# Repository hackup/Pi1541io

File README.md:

# PI1541 IO Adapter

This is an IO adapter board for the Raspberry Pi 3, based on the awesome [Pi1541
project](https://cbm-pi1541.firebaseapp.com/) by Steve White. It is currently
very much work in progress. **USE AT YOUR OWN RISK!**

Details of the adapter board development are [documented on hackup.net](https://www.hackup.net/tag/pi1541/). The [Gerber files](gerber/Pi1541io-rev4.zip) for the latest stable revision are included in the repository. Also, the boards are ready to be ordered directly from [PCBWay](https://www.pcbway.com/project/shareproject/Pi1541_IO_Adapter__Rev_4.html?inviteid=78096) or [DirtyPCBs](https://dirtypcbs.com/store/designer/details/hackup/6112/pi1541-io-adapter-rev-4).

## Revisions

### Revision 4
This revision of the board resolves the I2C power supply issues of the previous version. All relevant aspects of the I2C header must now be configured using solder bridges on the bottom side of the PCB.

* Select either 3.3V or 5V power supply. (If in doubt, use 3.3V!)
* Pin order: Vin-GND-SCL-SDA or GND-Vin-SCL-SDA
* Chose either I2C bus 0 or 1

See [here](https://www.hackup.net/2018/07/pi1541io-revision-4/) for more details.

### Revision 3
The third revision features an I2C header for connecting a SSD1306 based OLED display module. The power line on this header is connected to 5V of the Raspberry. This is the preferred option for display modules that bring their own 3.3V regulator. Unfortunately, there seem to be modules out there without such a regulator. Connecting one of those to 5V will damage both the display and the Raspberry.

This issue is resolved in revision 4. So, unless you already have one of these boards you better skip directly to revision 4.

### Revision 2
The second revision features quite a few improvements, the most important one being optional support for the 7406 bus driver IC. For further details and instructions on how to assemble this board [see here](https://www.hackup.net/2018/06/pi1541io-revision-2/).

### Revision 1
A prototype batch of the first revision has been manufactured and [tested](https://www.hackup.net/2018/05/pi1541-io-adapter/). It is generally working but there are a few minor issues. The Gerber files for this revision are included, but I would currently recommend waiting for revision 2.

## License
[
](http://creativecommons.org/licenses/by-sa/4.0/)
This work is licensed under a
[Creative Commons Attribution-ShareAlike 4.0 International License](http://creativecommons.org/licenses/by-sa/4.0/)

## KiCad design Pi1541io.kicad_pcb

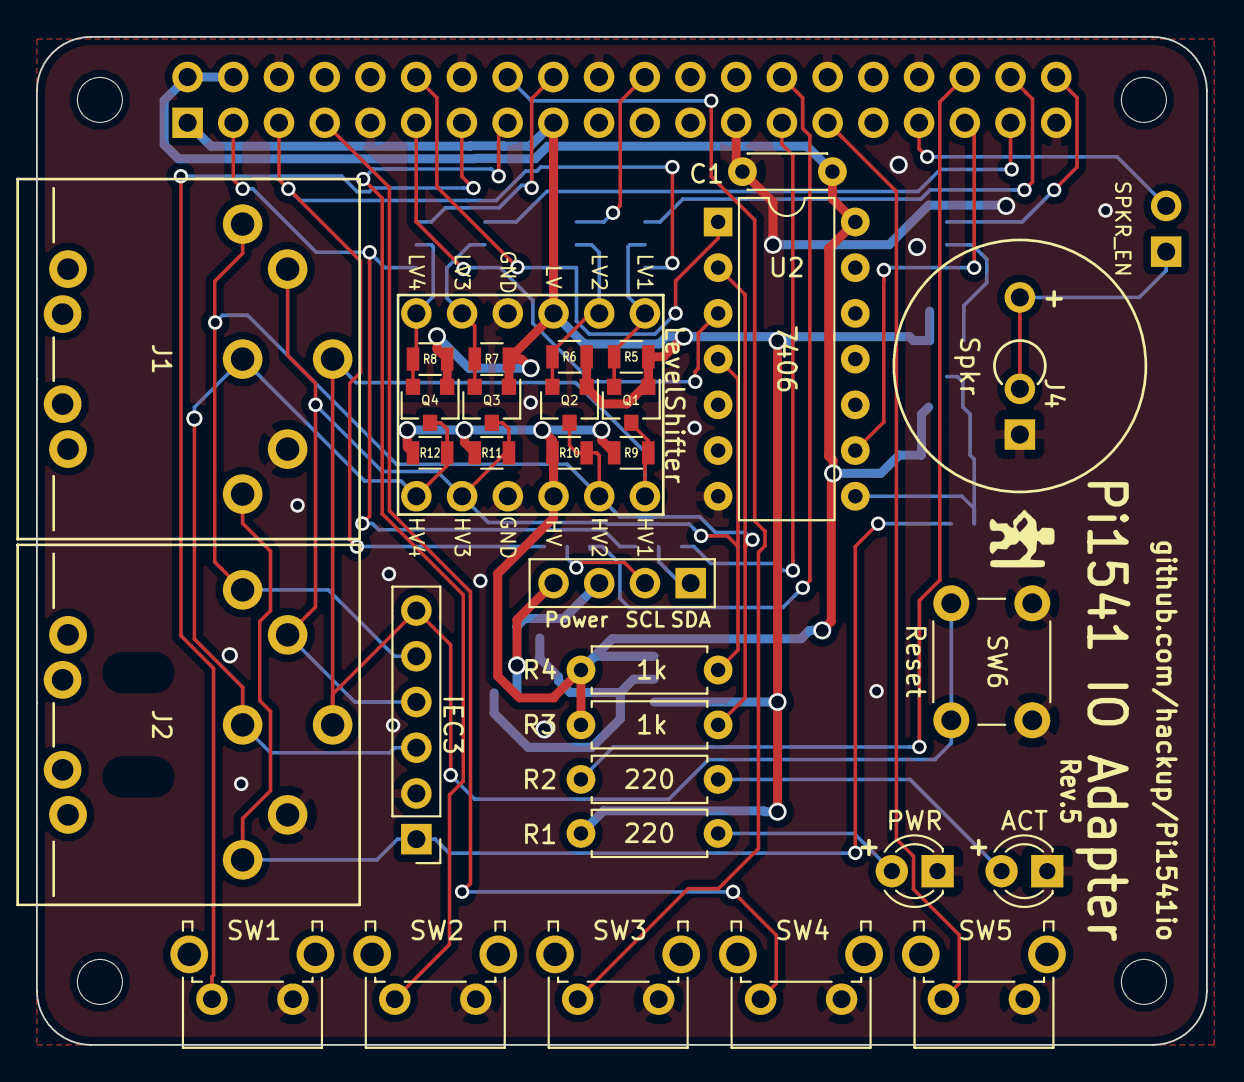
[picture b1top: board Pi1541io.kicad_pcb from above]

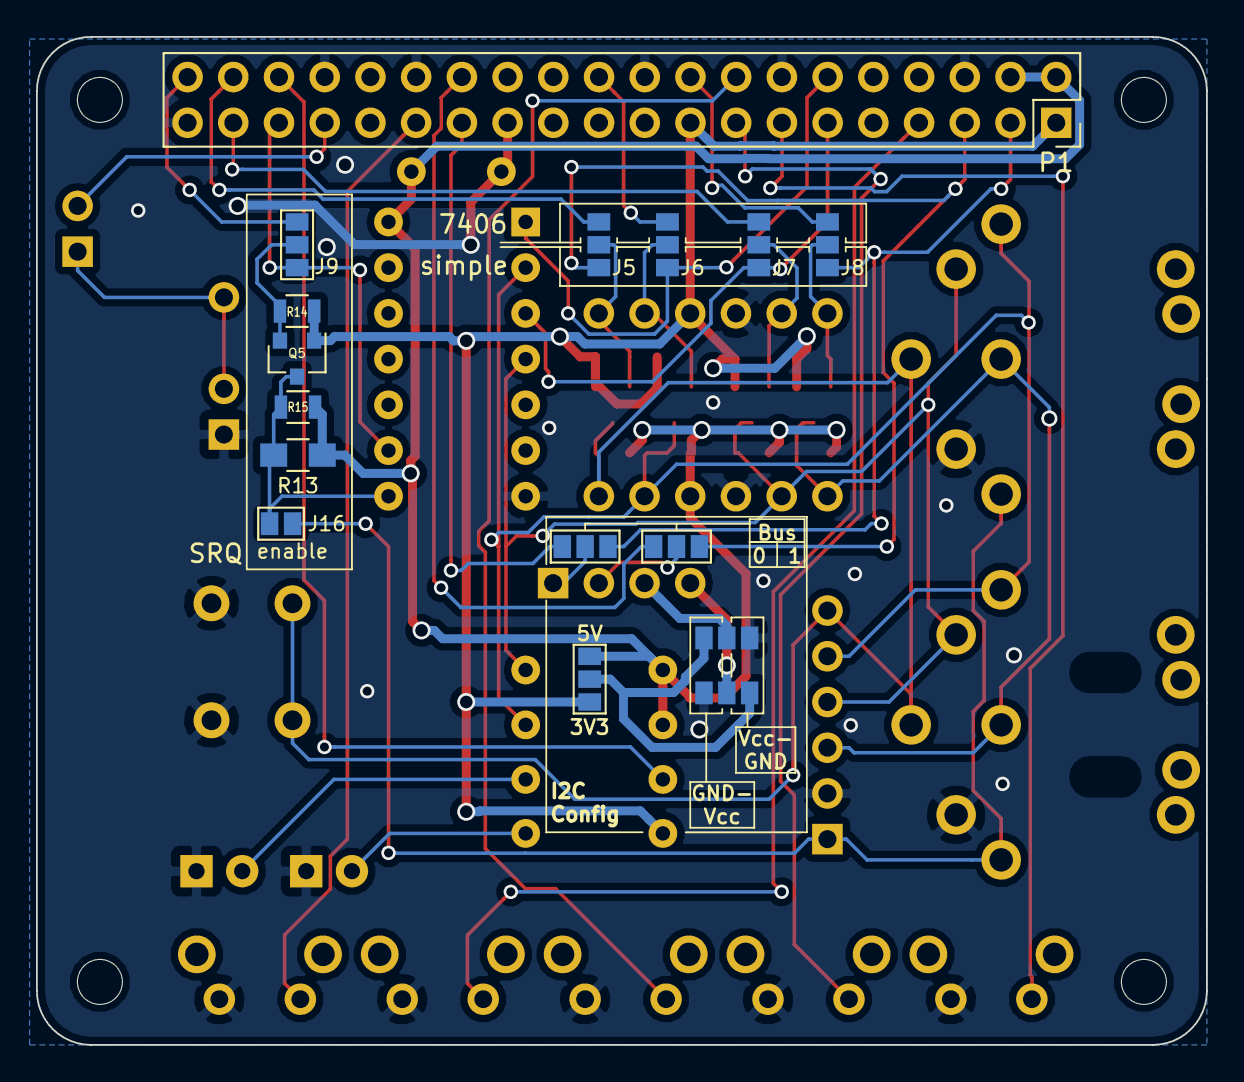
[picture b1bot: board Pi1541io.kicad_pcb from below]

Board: 2 copper layers, 65.0 x 56.0 mm, 56 parts (16 on the bottom side), 41 nets.

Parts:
C1: 100n; C_Disc_D4.3mm_W1.9mm_P5.00mm
D1: PWR; LED_D3.0mm
D2: ACT; LED_D3.0mm
J1: IEC1; DIN-6-Variable
J2: IEC2; DIN-6-Variable
J3: IEC3; Pin_Header_Straight_1x06_Pitch2.54mm
J4: ExtSpkr; Pin_Header_Straight_1x01_Pitch2.54mm
J5, J6, J7, J8, J9: GS3
J10, J13, J14, J15: SDA; GS3
J11: SCL; GS3
J12: I2C; Socket_Strip_Straight_1x04_Pitch2.54mm
J16: GS2
LS1: Spkr; Piezo Speaker 1407
MK1, MK2, MK3, MK4: M2.5; MountingHole_2.5mm
MK5, MK6: ZipTie; ZipTie_3.0mm
P1: Conn_02x20_Odd_Even; Socket_Strip_Straight_2x20_Pitch2.54mm
Q1, Q2, Q3, Q4, Q5: BSS138; SOT-23
R1, R2: 220; R_Axial_DIN0207_L6.3mm_D2.5mm_P7.62mm_Horizontal
R3, R4: 1k; R_Axial_DIN0207_L6.3mm_D2.5mm_P7.62mm_Horizontal
R5, R6, R7, R8, R9, R10, R11, R12, R14, R15: 10k; R_0805
R13: 1k; R_0805_HandSoldering
SW1, SW2, SW3, SW4, SW5: SW_Push; SW_Tactile_SPST_Angled_PTS645Vx83-2LFS
SW6: Reset; SW_PUSH_6mm
SW7: SPKR_EN; Pin_Header_Straight_2x01_Pitch2.54mm
U1: LevelShifter; LevelShifterModule4CH
U2: 7406; DIP-14_W7.62mm

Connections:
+3V3: J15.1, P1.1, P1.17, Q1.1, Q2.1, Q3.1, Q4.1, Q5.1, R1.1, R5.1, R6.1, R7.1, R8.1, R14.1, U1.3
+5V: C1.1, J15.3, P1.2, P1.4, R3.1, R4.1, R9.1, R10.1, R11.1, R12.1, R13.1, R15.1, U1.10, U2.14
/GPIO4(GCLK): P1.7, SW4.2
/GPIO5: P1.29, SW5.2
/GPIO13(PWM1): P1.33, SW7.2
/GPIO16: P1.36, R2.1
/GPIO22(GEN3): P1.15, SW2.2
/GPIO23(GEN4): P1.16, SW3.2
/GPIO27(GEN2): P1.13, SW1.2
ATN: J1.3, J2.3, J3.3, Q4.3, R12.2, U1.7
ATN_3V: J8.2, Q4.2, R8.2, U1.6
ATN_BD: J8.1, J10.3, P1.3
ATN_IN: J8.3, P1.18
CLK: J1.4, J2.4, J3.4, Q3.3, R4.2, R11.2, U1.8, U2.4
CLK_3V: J7.2, Q3.2, R7.2, U1.5
CLK_BD: J7.1, P1.11, U2.3
CLK_IN: J7.3, P1.37
DATA: J1.5, J2.5, J3.5, Q2.3, R3.2, R10.2, U1.11, U2.2
DATA_3V: J6.2, Q2.2, R6.2, U1.2
DATA_BD: J6.1, P1.12, U2.1
DATA_IN: J6.3, P1.22
GND: C1.2, D1.1, D2.1, J1.2, J2.2, J3.2, J13.3, J14.3, LS1.2, P1.6, P1.9, P1.14, P1.20, P1.25, P1.30, P1.34, P1.39, SW1.1, SW2.1, SW3.1, SW4.1, SW5.1, SW6.2, U1.4, U1.9, U2.7
I2C0_SCL: J11.1, P1.28
I2C0_SDA: J10.1, P1.27
I2C1_SCL: J5.1, J11.3, P1.5
unnamed: D1.2, R1.2
unnamed: D2.2, R2.2
unnamed: J4.1, LS1.1, SW7.1
unnamed: J10.2, J12.1
unnamed: J11.2, J12.2
unnamed: J12.3, J13.2
unnamed: J12.4, J14.2
unnamed: J13.1, J14.1, J15.2
unnamed: J16.2, Q5.3, R13.2, R15.2, U2.8
RESET: J1.6, J2.6, J3.6, Q1.3, R9.2, SW6.1, U1.12
RESET_3V: J5.2, Q1.2, R5.2, U1.1
RESET_IN: J5.3, P1.38
SRQ: J1.1, J2.1, J3.1, J16.1
SRQ_3V: J9.2, Q5.2, R14.2
SRQ_BD: J9.1, P1.35, U2.9
SRQ_IN: J9.3, P1.40

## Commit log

2018-05-09 Initial commit.
2018-05-09 Added speaker and activity LED.
2018-05-09 Meta data.
2018-05-09 Fixed page size.
2018-05-10 Added second IEC port and reset button.
2018-05-10 Added readme.
2018-05-10 Gerber export.
2018-05-10 Added preview images.
2018-05-18 Adding alternate TXS0108 level shifter module to choose from.
2018-05-18 Reserved SRQ pin.
2018-05-18 Fix.
2018-05-23 Added 7406 driver for outgoing signals.
2018-05-24 Preparing for release.
2018-05-24 Silk screen corrections. Re-added reset button.
2018-05-24 Added rev.2 preview rendering.
2018-05-24 Discrete components to optionally replace the level shifter module.
2018-05-25 Added SRQ label.
2018-05-25 Added optional components for reserved SRQ pins.
2018-05-25 Project spelling.
2018-05-25 Added missing values.
2018-05-25 Readme updated.
2018-05-25 Use wider footprint for cap.
2018-05-26 Revision 2 finalized.
2018-06-04 Trying to fix libraries and paths.
2018-06-04 Commited rev.2 Gerber files.
2018-06-04 Updated readme.
2018-06-05 Corrected image sizes.
2018-06-05 Added plaingtext license file.
2018-06-05 Added I2C display connector.
2018-06-12 Fine tuning I2C connector position.
2018-06-13 Updated page info.
2018-06-13 Preparing for revision 3.
2018-07-03 Kicad upgrade.
2018-07-03 Use 3.3V instead of 5V on I2C header.
2018-07-05 Preparing revision 4.
2018-07-06 I2C power pins now configurable.
2018-07-08 Both voltage and pin order now configurable.
2018-08-13 Added current schematics as PDF document.
2018-08-13 Fixed readme.
2018-08-28 Added I2C config example image.
2018-08-28 KiCAD 5.0.0.
2018-08-28 Added HTML BOM export.
2018-09-04 Added additional drill holes for DIN connectors and polarity indicator for LEDs.
2018-09-21 Relocated reset button.
2018-09-21 Added ziptie holes.
2018-10-04 Added links to PCB fabs.
2018-10-05 Moved LEDs, texts, reset button, and speaker.
2018-10-05 Marked LED anodes.
2018-10-05 Rev.5 preview image.
2018-10-08 Improved ziptie holes.
2018-10-16 Shuffling layout to move the display connector.
2018-10-18 Added an additional solder bridge that is now needed to connect the SRQ line from the bus. This closes #1.
2018-10-18 Added footprint.
2018-10-18 Optimized silk screen.
2018-11-01 Fine tuning.
2018-11-01 Ready for next revision.
